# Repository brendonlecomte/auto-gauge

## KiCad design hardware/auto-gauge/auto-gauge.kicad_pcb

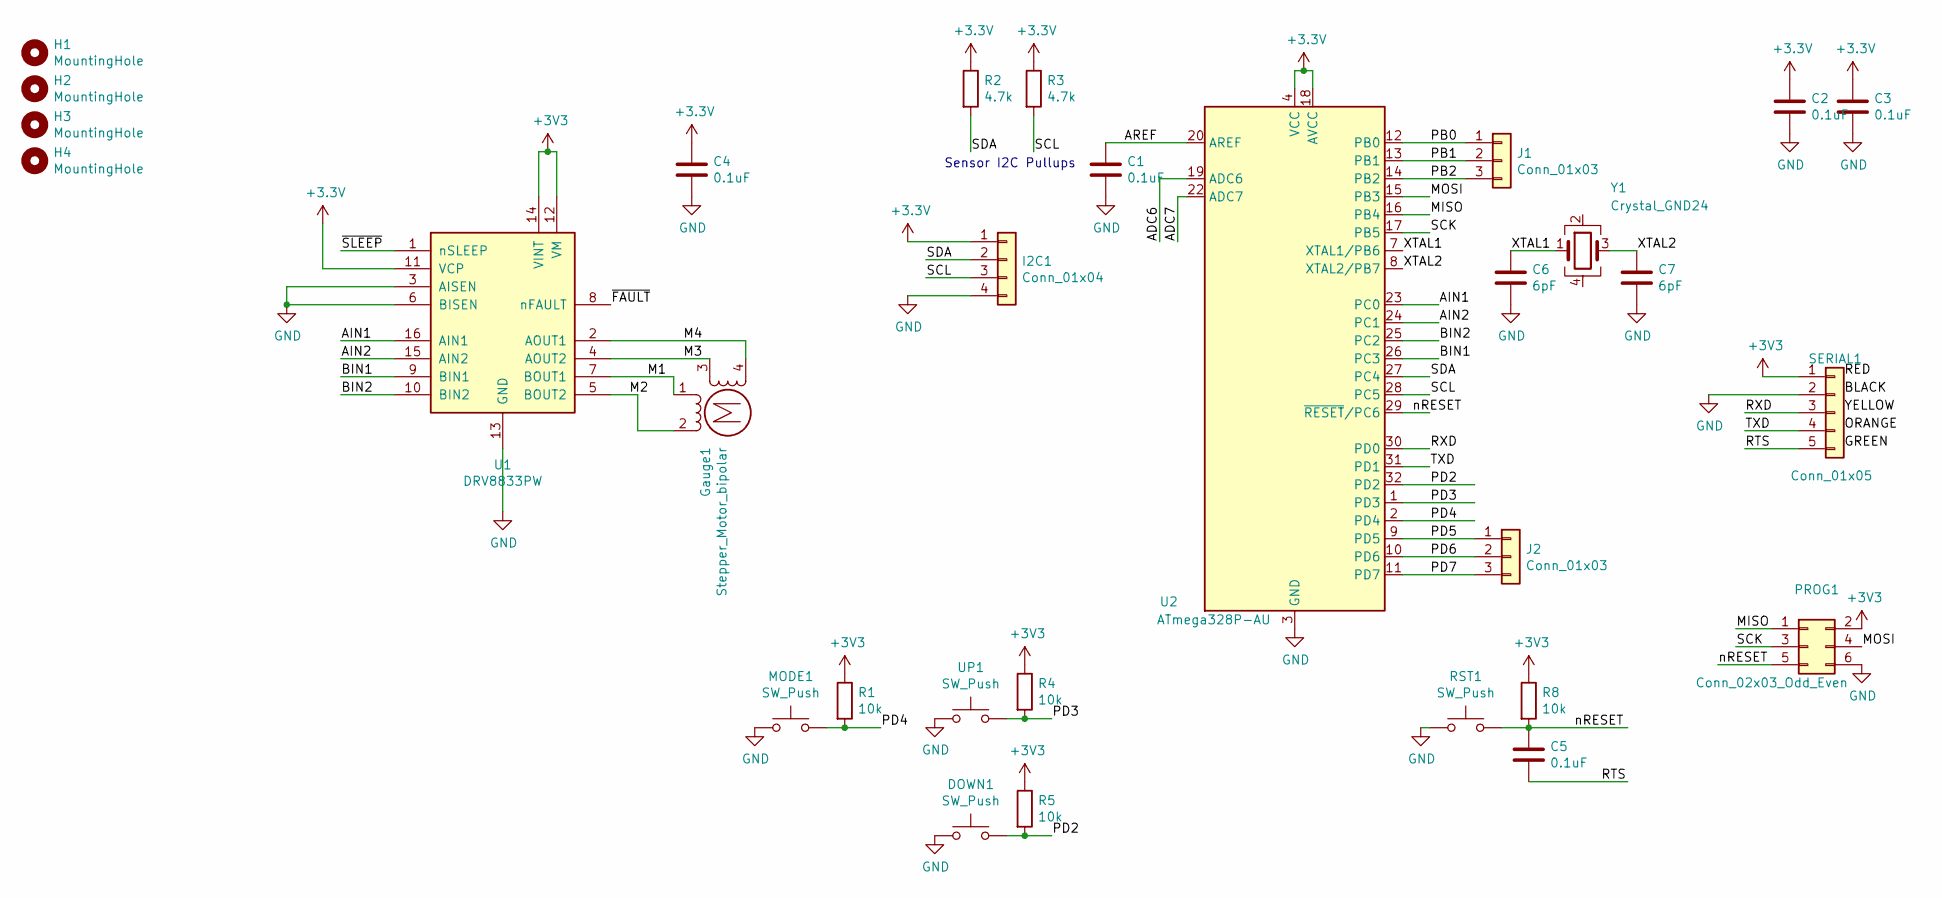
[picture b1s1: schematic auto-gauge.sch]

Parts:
C1, C2, C3, C4, C5: 0.1uF; C_0603_1608Metric; LCSC C14663
C6, C7: 6pF; C_0603_1608Metric; LCSC C37474
DOWN1: SW_Push; SW_SPST_TL3342; LCSC C318884
Gauge1: Stepper_Motor_bipolar; Auto-Stepper-Test
H1, H2, H3, H4: MountingHole; MountingHole_2.2mm_M2
I2C1: Conn_01x04; PinHeader_1x04_P2.54mm_Vertical
J1, J2: Conn_01x03; PinHeader_1x03_P2.54mm_Vertical
MODE1: SW_Push; SW_SPST_TL3342; LCSC C318884
PROG1: Conn_02x03_Odd_Even; PinHeader_2x03_P2.54mm_Vertical
R1, R4, R5, R8: 10k; R_0603_1608Metric; LCSC C25197
R2, R3: 4.7k; R_0603_1608Metric; LCSC C23162
RST1: SW_Push; SW_SPST_TL3342; LCSC C318884
SERIAL1: Conn_01x05; PinHeader_1x05_P2.54mm_Vertical
U1: DRV8833PW; TSSOP-16_4.4x5mm_P0.65mm; LCSC C50506
U2: ATmega328P-AU; TQFP-32_7x7mm_P0.8mm; LCSC C14877
UP1: SW_Push; SW_SPST_TL3342; LCSC C318884
Y1: Crystal_GND24; Crystal_SMD_Abracon_ABM8G-4Pin_3.2x2.5mm; LCSC C255906

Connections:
/ADC6: U2.19 (ADC6)
/ADC7: U2.22 (ADC7)
/AIN1: U1.16 (AIN1), U2.23 (PC0)
/AIN2: U1.15 (AIN2), U2.24 (PC1)
/AREF: C1.1, U2.20 (AREF)
/BIN1: U1.9 (BIN1), U2.26 (PC3)
/BIN2: U1.10 (BIN2), U2.25 (PC2)
/M1: Gauge1.1, U1.7 (BOUT1)
/M2: Gauge1.2 (-), U1.5 (BOUT2)
/M3: Gauge1.3, U1.4 (AOUT2)
/M4: Gauge1.4, U1.2 (AOUT1)
/MISO: PROG1.1, U2.16 (PB4)
/MOSI: PROG1.4, U2.15 (PB3)
/PB0: J1.1, U2.12 (PB0)
/PB1: J1.2, U2.13 (PB1)
/PB2: J1.3, U2.14 (PB2)
/PD2: DOWN1.2, R5.2, U2.32 (PD2)
/PD3: R4.2, U2.1 (PD3), UP1.2
/PD4: MODE1.2, R1.2, U2.2 (PD4)
/PD5: J2.1, U2.9 (PD5)
/PD6: J2.2, U2.10 (PD6)
/PD7: J2.3, U2.11 (PD7)
/RTS: C5.2, SERIAL1.5
/RXD: SERIAL1.3, U2.30 (PD0)
/SCK: PROG1.3, U2.17 (PB5)
/SCL: I2C1.3, R3.2, U2.28 (PC5)
/SDA: I2C1.2, R2.2, U2.27 (PC4)
/TXD: SERIAL1.4, U2.31 (PD1)
/XTAL1: C6.1, U2.7 (XTAL1/PB6), Y1.1
/XTAL2: C7.1, U2.8 (XTAL2/PB7), Y1.3
/nRESET: C5.1, PROG1.5, R8.2, RST1.2, U2.29 (~RESET~/PC6)
/~FAULT: U1.8 (nFAULT)
/~SLEEP: U1.1 (nSLEEP)
GND: C1.2, C2.2, C3.2, C4.2, C6.2, C7.2, DOWN1.1, I2C1.4, MODE1.1, PROG1.6, RST1.1, SERIAL1.2, U1.3 (AISEN), U1.6 (BISEN), U1.13 (GND), U2.3 (GND), U2.5 (GND), U2.21 (GND), UP1.1

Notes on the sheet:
Sensor I2C Pullups

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
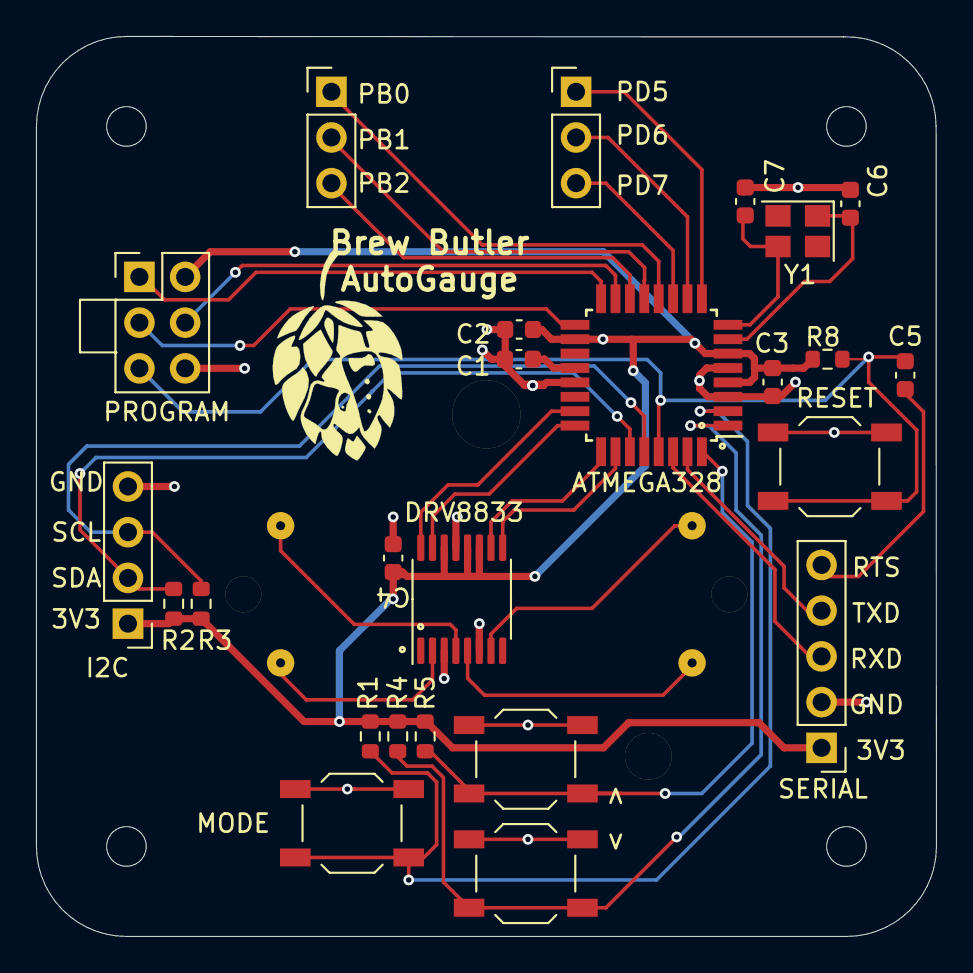
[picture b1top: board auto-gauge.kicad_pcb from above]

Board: 2 copper layers, 50.0 x 50.0 mm, 30 parts (0 on the bottom side), 31 nets.

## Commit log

2020-09-13 [HW] Proto PCB done. Ordered
2020-09-14 [FW] Init project. Zephyr style dir
2020-09-18 [BOARD] Autogauge custom board skeleton
2020-09-18 [USB] CDC basic enumeration
2020-09-19 [BOARD] Minimum flags for UART logging
2020-09-19 [BOARD] Tidy up pinmux. Add debug to main
2020-09-19 [BOARD] minimum conf for USB logging
2020-11-14 dump commit due to computer being erased
2021-10-20 arduino dummy/test. New board using atmega328 for jlcpcb asm
2021-10-20 gnd pour, remove middle layers, DRC for jlcpcb
2021-10-20 add brewbutler logo to silkscreens
2021-11-04 Ordered from JLCPCB
